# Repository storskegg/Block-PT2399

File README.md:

# Block-PT2399

A simple delay/echo design block based on the venerable PTC PT2399.

## Features

- Star Grounds: This board features a 2-star ground configuration
    1. All ground connections from and relating directly to the PT2399, and its
       dedicated power supply (`7805`) have their own trace to the negative lead
       on the `7805`'s `100uF` bypass capacitor.
    2. The above ground star, and all other ground connections (e.g. JFET
       impedance buffer) have their own traces back to `Sig_gnd`.
- Onboard regulation: The PT2399 is a particularly noisy beast, and must have
  its own power rail. As such, this board has its own 7805 regulator, and bypass
  capacitor (`100uF` located as close to the PT2399 as possible, while
  facilitating the star ground to the chip's supporting circuitry, and mfr's
  fabrication constraints.)

## Background

I've been working on a blues harp preamp for a buddy, and have been working on
the design in logical blocks that more or less get strung together. (It makes a
lot of sense when looking at valve gain stages, which are all basically the same
circuit repeated, maybe with different component values.) He mentioned wanting
delay or echo, and so I put this together. It is not a ground-up design, but
rather one that was inspired by the countless examples of using the PT2399
that you can find in the wild. (Sometimes it's better to stand on the shoulders
of giants.)

Anyhow, I decided to do up a board for ease of use in future projects.

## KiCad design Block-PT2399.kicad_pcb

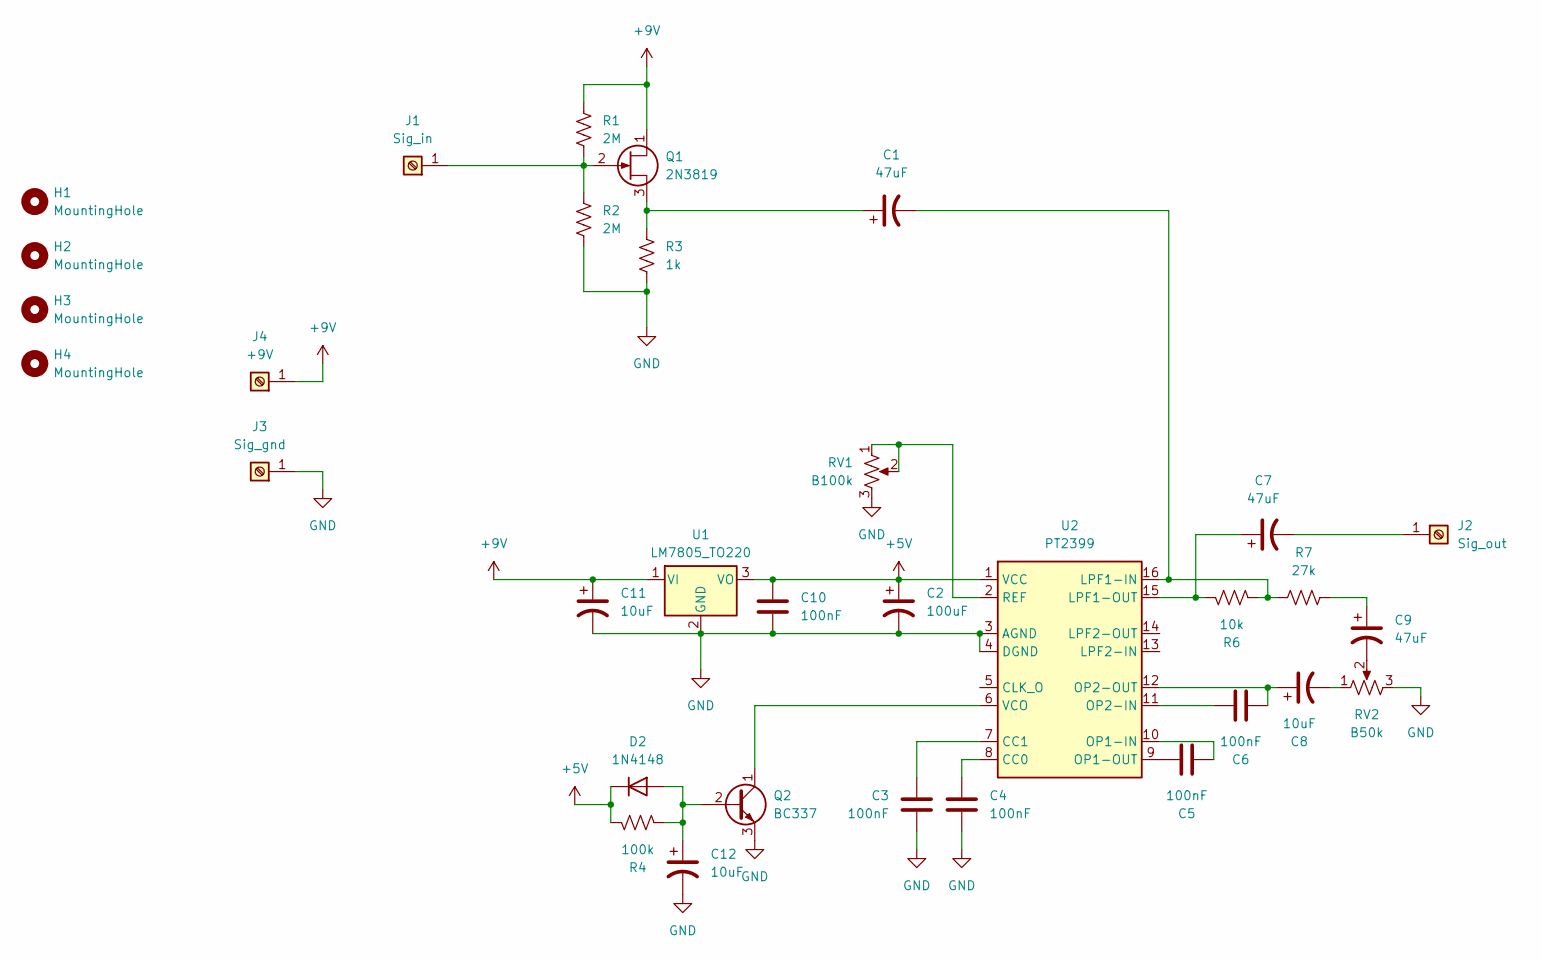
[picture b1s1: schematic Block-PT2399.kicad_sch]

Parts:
C1, C7, C9: 47uF; CP_Radial_D5.0mm_P2.00mm
C2: 100uF; CP_Radial_D5.0mm_P2.50mm
C3, C4, C5, C6: 100nF; C_Disc_D4.3mm_W1.9mm_P5.00mm
C8: 10uF; CP_Radial_D4.0mm_P1.50mm
C10: 100nF; C_Disc_D3.0mm_W1.6mm_P2.50mm
C11: 10uF; CP_Radial_D5.0mm_P2.00mm
C12: 10uF; CP_Radial_D4.0mm_P2.00mm
D2: 1N4148; D_DO-35_SOD27_P7.62mm_Horizontal
H1, H2, H3, H4: MountingHole; MountingHole_2.2mm_M2
J1: Sig_in; TerminalBlock_MetzConnect_360271_1x01_Horizontal_ScrewM3.0_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
J2: Sig_out; TerminalBlock_MetzConnect_360271_1x01_Horizontal_ScrewM3.0_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
J3: Sig_gnd; TerminalBlock_MetzConnect_360271_1x01_Horizontal_ScrewM3.0_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
J4: +9V; TerminalBlock_MetzConnect_360271_1x01_Horizontal_ScrewM3.0_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
Q1: 2N3819; TO-92_Inline_Wide
Q2: BC337; TO-92_Inline
R1, R2: 2M; R_Axial_DIN0207_L6.3mm_D2.5mm_P10.16mm_Horizontal
R3: 1k; R_Axial_DIN0207_L6.3mm_D2.5mm_P10.16mm_Horizontal
R4: 100k; R_Axial_DIN0204_L3.6mm_D1.6mm_P5.08mm_Horizontal
R6: 10k; R_Axial_DIN0207_L6.3mm_D2.5mm_P10.16mm_Horizontal
R7: 27k; R_Axial_DIN0207_L6.3mm_D2.5mm_P10.16mm_Horizontal
RV1: B100k; Potentiometer_Bourns_3266Y_Vertical
RV2: B50k; Potentiometer_Bourns_3266Y_Vertical
U1: LM7805_TO220; TO-220-3_Vertical
U2: PT2399; DIP-16_W7.62mm

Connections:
+5V: C2.1, C10.1, D2.1 (K), R4.2, U1.3 (VO), U2.1 (VCC)
+9V: C11.1, J4.1, Q1.1 (D), R1.1, U1.1 (VI)
GND: C2.2, C3.2, C4.2, C10.2, C11.2, C12.2, J3.1, Q2.3 (E), R2.2, R3.2, RV1.3, RV2.3, U1.2 (GND), U2.3 (AGND), U2.4 (DGND)
unnamed: C8.2, RV2.1
unnamed: C9.1, R7.2
unnamed: C9.2, RV2.2
unnamed: C12.1, D2.2 (A), Q2.2 (B), R4.1
unnamed: J1.1, Q1.2 (G), R1.2, R2.1
unnamed: C7.2, J2.1
unnamed: C1.1, Q1.3 (S), R3.1
unnamed: Q2.1 (C), U2.6 (VCO)
unnamed: C4.1, U2.8 (CC0)
unnamed: C3.1, U2.7 (CC1)
unnamed: C1.2, R6.2, R7.1, U2.16 (LPF1-IN)
unnamed: C7.1, R6.1, U2.15 (LPF1-OUT)
unnamed: C5.1, U2.10 (OP1-IN)
unnamed: C5.2, U2.9 (OP1-OUT)
unnamed: C6.1, U2.11 (OP2-IN)
unnamed: C6.2, C8.1, U2.12 (OP2-OUT)
unnamed: RV1.1, RV1.2, U2.2 (REF)

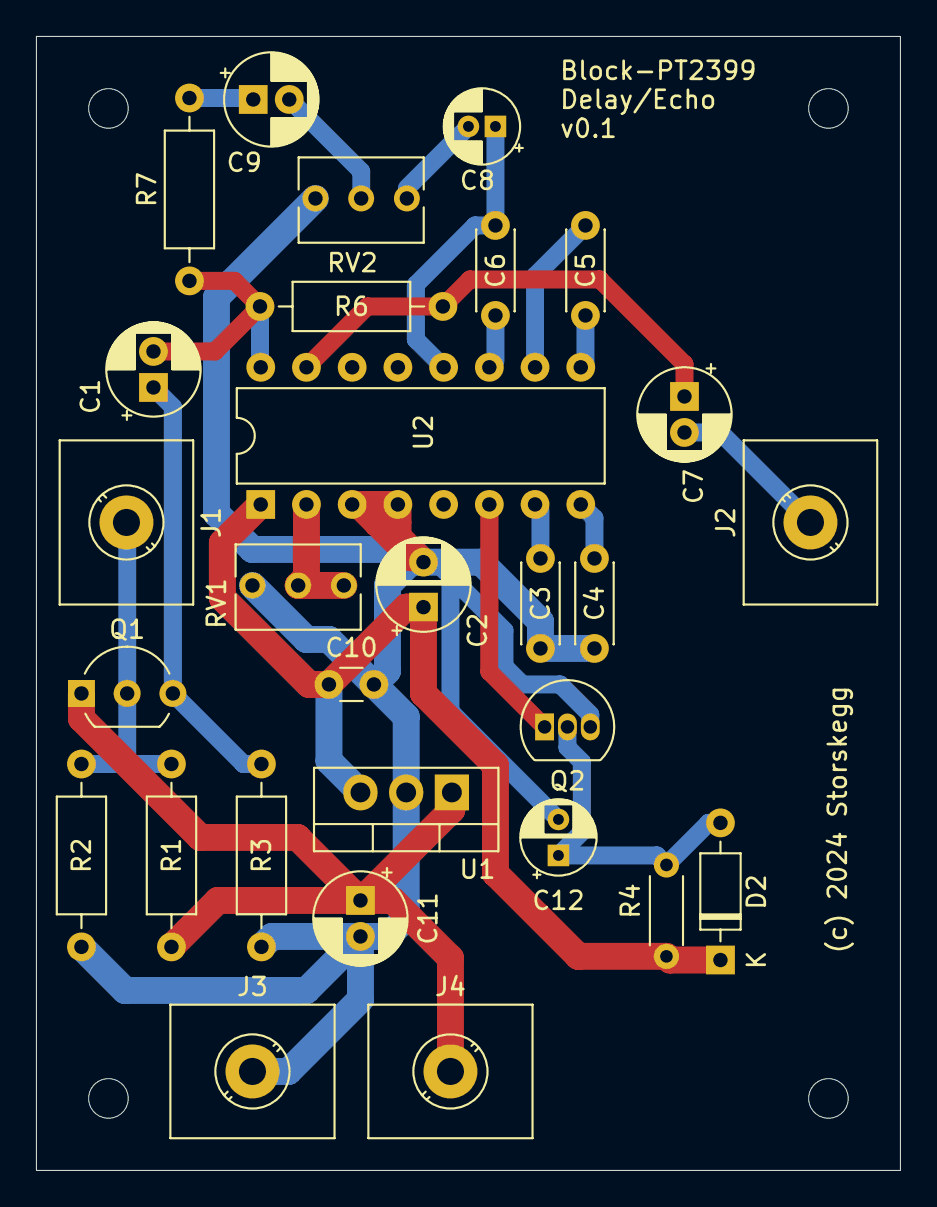
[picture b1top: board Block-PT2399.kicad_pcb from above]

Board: 2 copper layers, 48.0 x 63.0 mm, 33 parts (0 on the bottom side), 20 nets.

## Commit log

2024-10-14 Add the project files
2024-10-14 Add features section
2024-10-18 implement pin-2 hack and anti-latch
2025-01-22 working on redoing board size and layout, dropped the diode
2025-01-22 widen traces to lower trace impedances
2025-01-22 update gitignore

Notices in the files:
Block-PT2399.kicad_pcb:
(c) 2024 Storskegg
